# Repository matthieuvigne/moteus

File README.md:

# nautilus - a fork for moteus brushless servo driver

`nautilus` is a direct fork of moteus's driver with modified shape and interface to fit inside MyActuator's RMDX motors
(Mini-Cheatah like design), as a replacement of their driver. The main modifications are:

 - use an SPI interface instead of CAN
 - secondary SPI port for external encoder
 - usage of the `CSD88599` half-bridges instead of individual MOSFET to reduce the number of components
 - modified board shape and layout to fit inside the motor
 - the design is done using KiCad instead of Eagle

All new files are in the `nautilus` folder.

# moteus brushless servo #

This contains full designs for the moteus brushless servo actuator,
including firmware and PCBs.

**WARNING**: This is not just a software project.  It includes designs
for moderately high power electronics.  It has not yet burned down my
(or anyone's that I know of) house, but there are no guarantees.

# Specifications #

| Name                  | Value          |
|-----------------------|----------------|
| Voltage Input         | 10-44V         |
| Peak Electrical Power | 500W           |
| Mass                  | 14.2g          |
| Control Rate          | 15-40kHz       |
| PWM Switching Rate    | 15-60kHz       |
| CPU                   | 170Mhz STM32G4 |
| Peak phase current    | 100A           |
| Communications        | 5Mbps CAN-FD   |
| Dimensions            | 46x53mm        |

Assembled and tested boards can be purchased at https://mjbots.com/products/moteus-r4-11

# Directory structure #

* hw/ - hardware (mechanical and electrical designs)
  * controller/ - PCB design for servo controller
* fw/ - firmware for brushless controller
* lib/ - client side software
* utils/ - diagnostic tools
* tools/ - bazel build configure
* docs/ - documentation

# Documentation #

* [Getting Started](docs/getting_started.md)
* [Reference](docs/reference.md)

# Misc #

 * travis-ci 

# How to support moteus development #

The easiest way to support development the moteus hardware and firmware is as follows:

1) Buy things from https://mjbots.com
2) Build awesome machines!

That's it!  If for some reason you want to go above and beyond, you can sponsor mjbots through github: https://github.com/sponsors/mjbots

# License #

All files contained in this repository, unless otherwise noted, are
available under an Apache 2.0 License:
https://www.apache.org/licenses/LICENSE-2.0

# Trademark #

mjbots Robotic Systems LLC owns and protects the "mjbots" and "moteus" trademarks in many jurisdictions.

If you want to use these names in your project or product, please read the [Trademark Policy](https://mjbots.com/trademark-policy)

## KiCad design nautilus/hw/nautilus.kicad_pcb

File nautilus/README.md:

# How to compile and flash the firmware

## Installing dependencies

```sudo dnf install patch openocd arm-none-eabi-binutils-cs```

## Building the firmware

The firmware can be built by the following command:

```./tools/bazel test --config=target //fw:nautilus```

The bootloader also needs to be built (typically only once):

```./tools/bazel test --config=target //fw:can_bootloader ```

## Flashing

## Setting STM32 option bytes

Pin PB8 (boot) is used for I2C, thus pulled up. Hence, for the firmware to start running, the STM32 option bytes must be changed. This requires the software STM32CubeProgrammer, and the following configuration: nSWBOOT0 unchecked, nBOOT0 checked.

## Flashing

Simply run the python script: `python fw/flash.py`

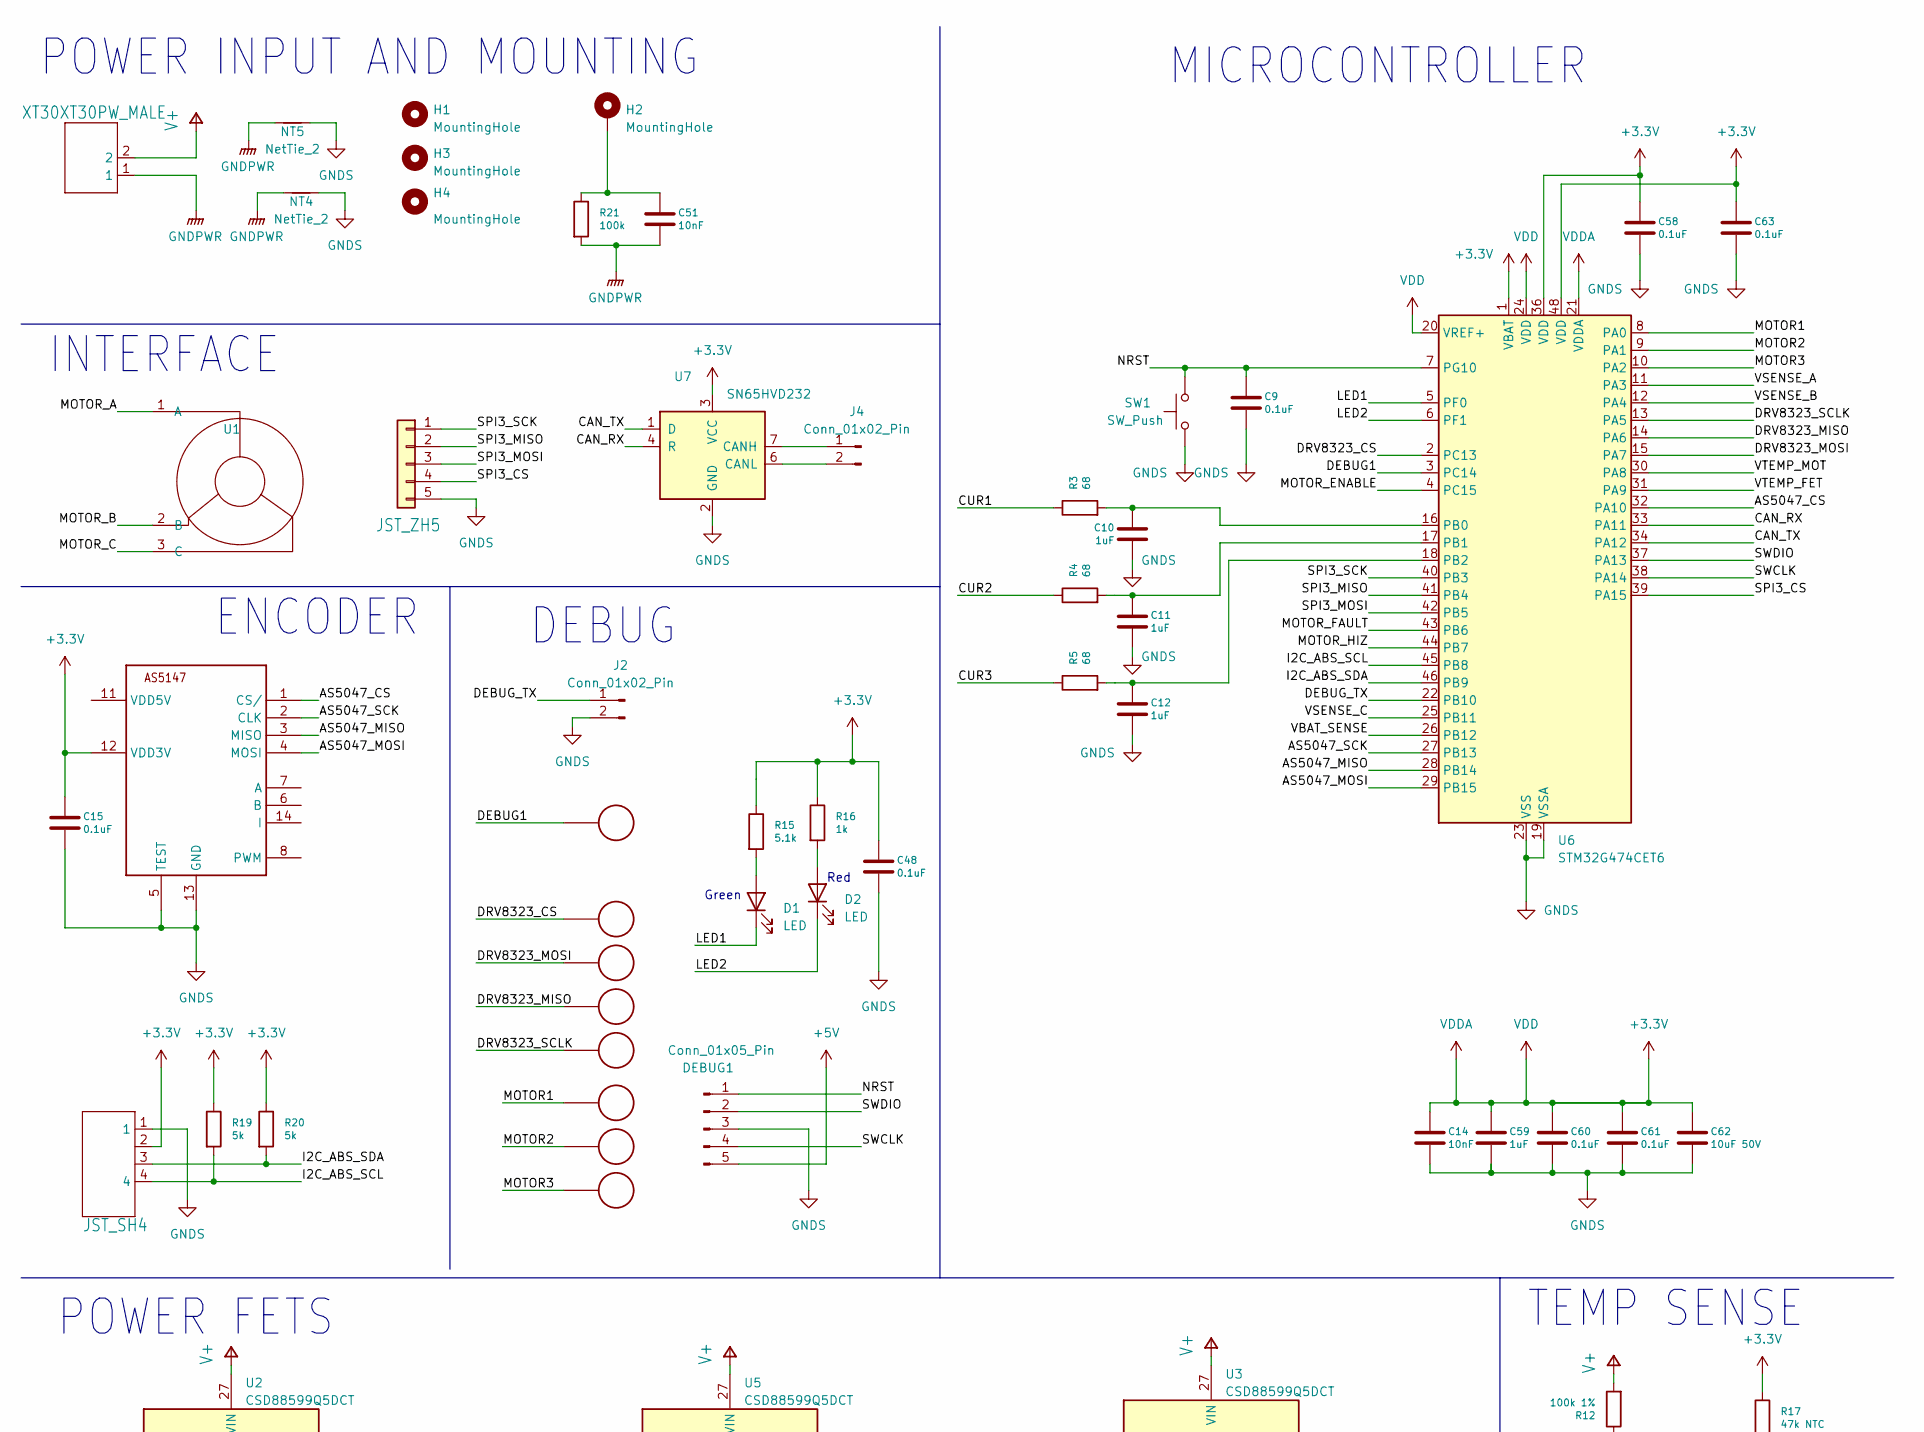
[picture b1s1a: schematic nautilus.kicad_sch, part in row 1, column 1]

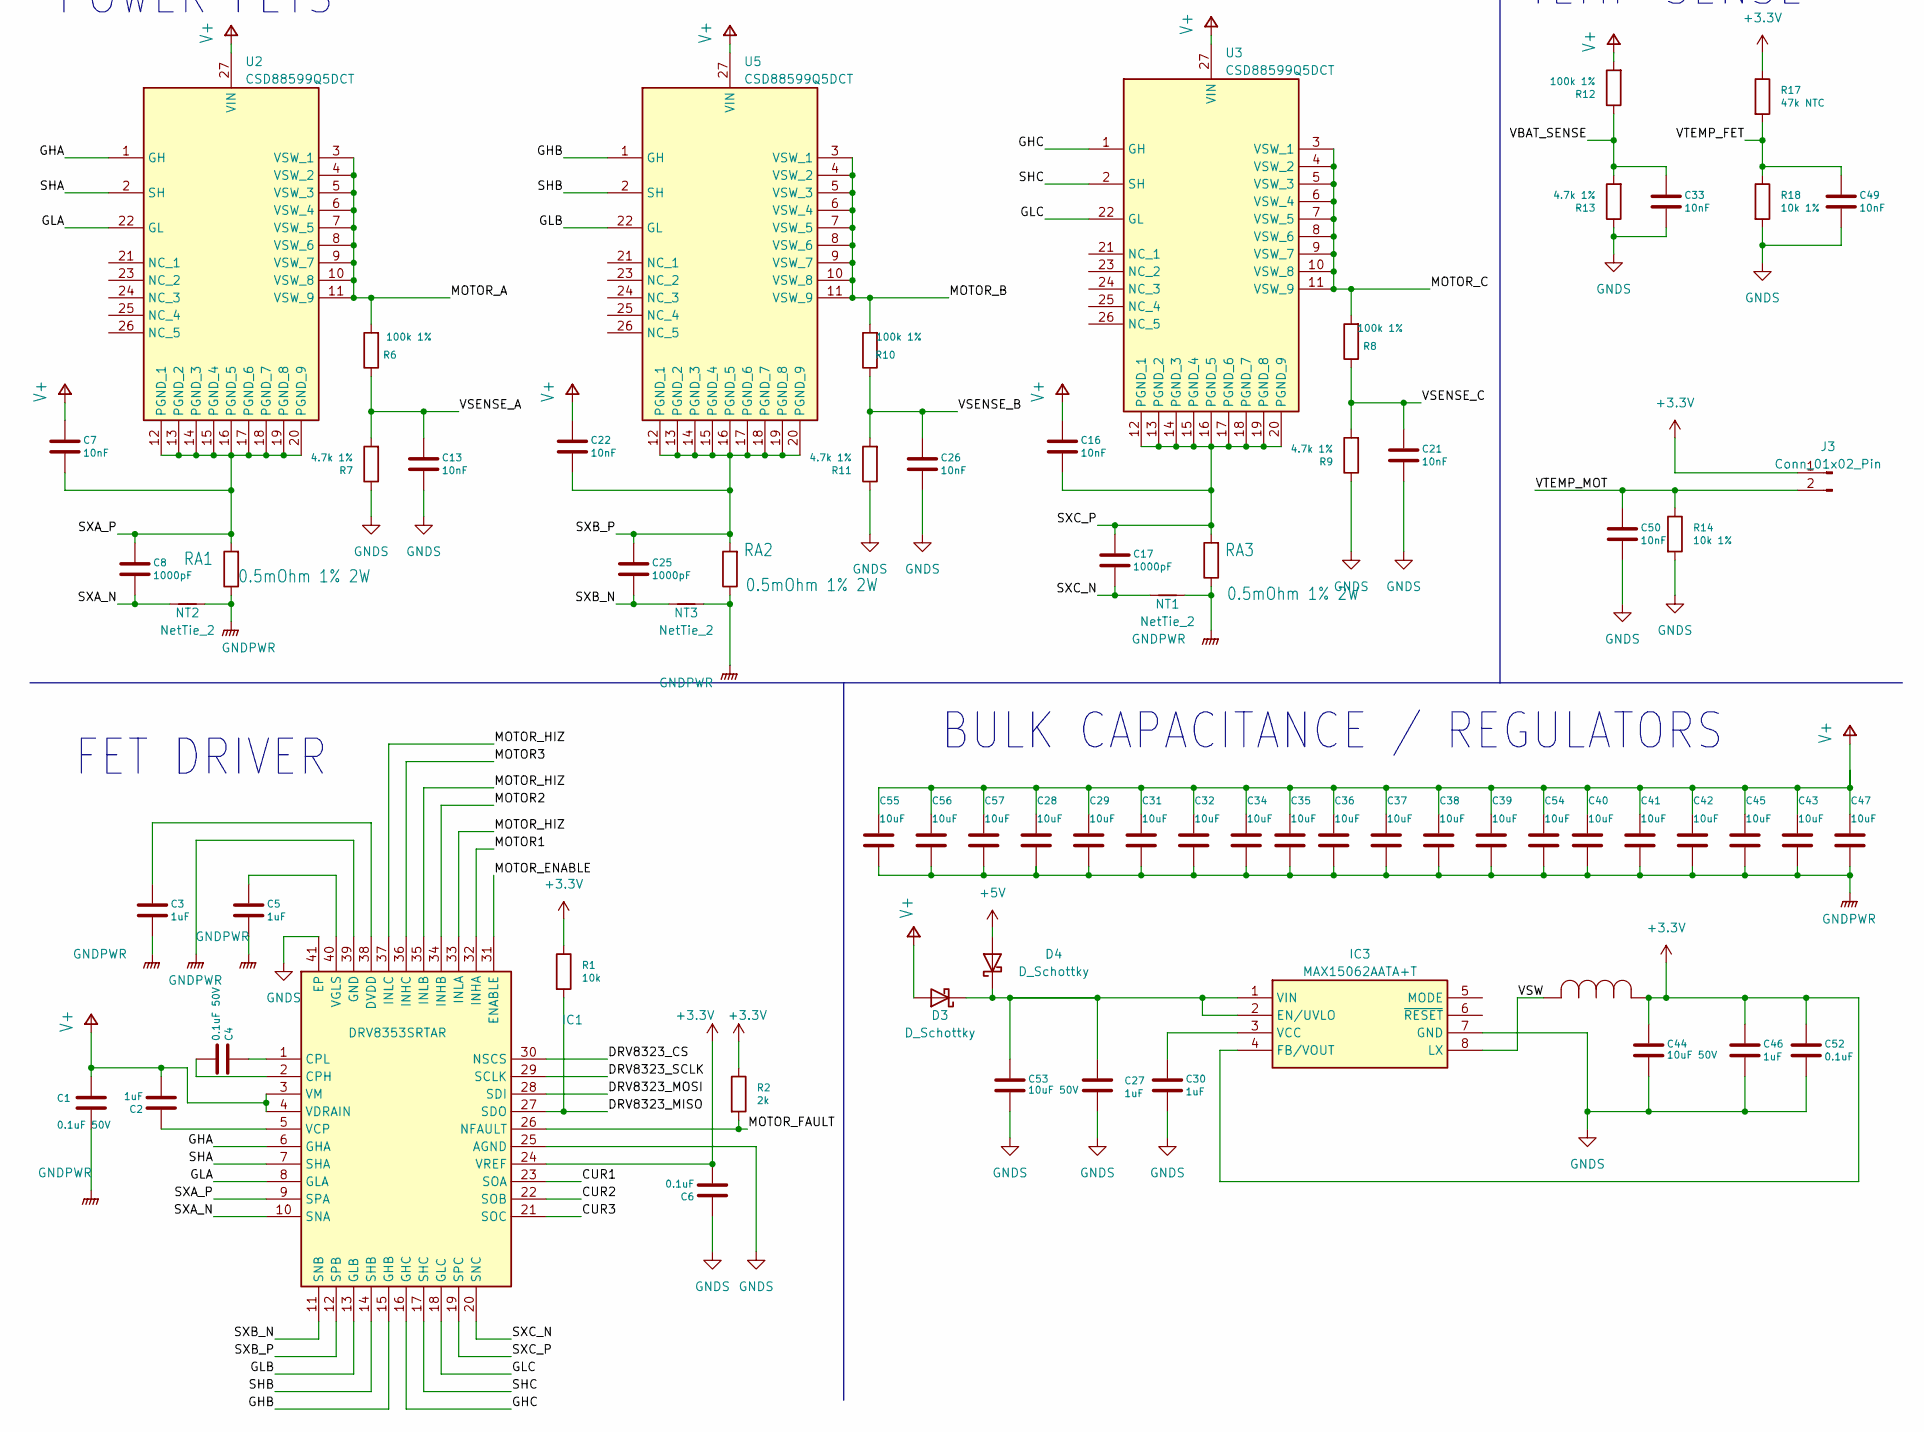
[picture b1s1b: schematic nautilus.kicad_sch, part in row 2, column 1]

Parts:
C1, C4: 0.1uF 50V; C_0402_1005Metric_Pad0.74x0.62mm_HandSolder; MPN CGA2B3X7R1H104K050BB
C2, C3, C5, C46, C59: 1uF; C_0402_1005Metric_Pad0.74x0.62mm_HandSolder; MPN MF-CAP-0402-1uF
C6, C9, C15, C48, C52, C58, C60, C61, C63: 0.1uF; C_0402_1005Metric_Pad0.74x0.62mm_HandSolder; MPN MF-CAP-0402-0.1uF
C7, C13, C14, C16, C21, C22, C26, C51: 10nF; C_0402_1005Metric_Pad0.74x0.62mm_HandSolder; MPN MF-CAP-0402-1nF
C8, C17, C25: 1000pF; C_0402_1005Metric_Pad0.74x0.62mm_HandSolder; MPN MF-CAP-0402-1nF
C10, C11, C12: 1uF; C_0402_1005Metric_Pad0.74x0.62mm_HandSolder; MPN MF-CAP-0402-1nF
C27, C30: 1uF; C_0402_1005Metric_Pad0.74x0.62mm_HandSolder; MPN MF-CAP-0603-1uF
C28, C29, C31, C32, C34, C35, C36, C37, C38, C39, C40, C41, C42, C43, C45, C47, C54, C55, C56, C57: 10uF; C_1206_3216Metric_Pad1.33x1.80mm_HandSolder; MPN CL31A106MBHNNNE; Mouser Part Number 187-CL31A106MBHNNNE
C33, C50: 10nF; C_0402_1005Metric_Pad0.74x0.62mm_HandSolder; MPN MF-CAP-0402-0.01uF
C44, C53, C62: 10uF 50V; C_1206_3216Metric_Pad1.33x1.80mm_HandSolder; MPN CL31A106MBHNNNE; Mouser Part Number 187-CL31A106MBHNNNE
C49: 10nF; C_0402_1005Metric_Pad0.74x0.62mm_HandSolder; MPN MF-CAP-0402-0.1uF
D1, D2: LED; LED_0805_2012Metric_Pad1.15x1.40mm_HandSolder
D3, D4: D_Schottky; D_SOD-123F; Mouser Part Number 833-SMD210PLQ-TP
DBG1: PAD24AWG_PAD; TestPoint_Pad_D1.0mm
DEBUG1: Conn_01x05_Pin; JST_SH_SM05B-SRSS-TB_1x05-1MP_P1.00mm_Horizontal
DRV_CS1: PAD24AWG_PAD; TestPoint_Pad_D1.0mm
DRV_MISO1: PAD24AWG_PAD; TestPoint_Pad_D1.0mm
DRV_MOSI1: PAD24AWG_PAD; TestPoint_Pad_D1.0mm
DRV_SCK1: PAD24AWG_PAD; TestPoint_Pad_D1.0mm
H1, H2, H3, H4: MountingHole; MountingHole-Plated
IC1: DRV8353SRTAR; QFN50P600X600X80-41N-D; Manufacturer_Part_Number DRV8353SRTAR; Mouser Part Number 595-DRV8353SRTAT
IC3: MAX15062AATA+T; MAX15062AATAT; Manufacturer_Part_Number MAX15062AATA+T; Mouser Part Number 700-MAX15062AATA+T
J1: XT30XT30PW_MALE; AMASS_XT30PW-M_1x02_P2.50mm_Horizontal
J2, J3: Conn_01x02_Pin; PinHeader_1x02_P2.54mm_Vertical
J4: Conn_01x02_Pin; Molex_PicoBlade_53047-0210_1x02_P1.25mm_Vertical
L1: SRN4018-220M; SRN4018220M; MANUFACTURER_PART_NUMBER SRN4018-330M; Mouser SRN4018
M1, M2, M3: PAD24AWG_PAD; TestPoint_Pad_D1.0mm
NT1, NT2, NT3, NT4, NT5: NetTie_2; NetTie-2_SMD_Pad0.5mm
R1: 10k; R_0402_1005Metric_Pad0.72x0.64mm_HandSolder; MPN MF-RES-0402-2K
R2: 2k; R_0402_1005Metric_Pad0.72x0.64mm_HandSolder; MPN MF-RES-0402-2K
R3, R4, R5: 68; R_0402_1005Metric_Pad0.72x0.64mm_HandSolder; MPN MF-RES-0402-22
R6, R8, R10, R12: 100k 1%; R_0402_1005Metric_Pad0.72x0.64mm_HandSolder; MPN RC0402FR-07100KL
R7, R9, R11, R13: 4.7k 1%; R_0402_1005Metric_Pad0.72x0.64mm_HandSolder; MPN RC0402FR-074K7L
R14, R18: 10k 1%; R_0402_1005Metric_Pad0.72x0.64mm_HandSolder; MPN RC0402FR-0710KL
R15: 5.1k; R_0402_1005Metric_Pad0.72x0.64mm_HandSolder; MPN MF-RES-0402-560
R16: 1k; R_0402_1005Metric_Pad0.72x0.64mm_HandSolder; MPN MF-RES-0402-560
R17: 47k NTC; R_0402_1005Metric_Pad0.72x0.64mm_HandSolder; MPN NCP15WB473F03RC; Mouser Part Number 81-NCP15WB473F03RC
R19, R20: 5k; R_0402_1005Metric_Pad0.72x0.64mm_HandSolder; MPN MF-RES-0402-2K
R21: 100k; R_0402_1005Metric_Pad0.72x0.64mm_HandSolder; MPN MF-RES-0402-2K
RA1, RA2, RA3: 0.5mOhm 1% 2W; R_2512_6332Metric_Pad1.40x3.35mm_HandSolder; MPN HCS1206FTL500; Mouser 504-MSMA2512R0005FGM
SPI1: JST_ZH5; JST_GH_SM05B-GHS-TB_1x05-1MP_P1.25mm_Horizontal; MPN S4B-ZR-SM4A-TF(LF)(SN)
SPI2: JST_SH4; JST_SH_SM04B-SRSS-TB_1x04-1MP_P1.00mm_Horizontal; MPN S4B-ZR-SM4A-TF(LF)(SN)
SW1: SW_Push; SW_SPST_B3U-1000P
U1: BrushlessMotor
U2, U3, U5: CSD88599Q5DCT; Q5DC_DMM; Manufacturer_Part_Number CSD88599Q5DCT; Mouser Part Number 595-CSD88599Q5DCT
U4: AS5147; TSSOP-14_4.4x5mm_P0.65mm; MPN AS5047P-ATSM
U6: STM32G474CET6; LQFP-48_7x7mm_P0.5mm; Mouser Part Number 511-STM32G474CET6
U7: SN65HVD232; SOIC-8_3.9x4.9mm_P1.27mm

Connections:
+3.3V: C6.2, C14.1, C15.1, C44.1, C46.1, C48.1, C52.1, C58.1, C59.1, C60.1, C61.1, C62.1, C63.1, IC1.24 (VREF), IC3.4 (FB/VOUT), J3.1, L1.1, R1.1, R2.1, R15.1, R16.1, R17.1, R19.1, R20.1, SPI2.2, U4.12 (VDD3V), U6.1 (VBAT), U6.20 (VREF+), U6.21 (VDDA), U6.24 (VDD), U6.36 (VDD), U6.48 (VDD), U7.3 (VCC)
+5V: D4.2 (A), DEBUG1.5
/AS5047_CS: U4.1 (CS/), U6.32 (PA10)
/AS5047_MISO: U4.3 (MISO), U6.28 (PB14)
/AS5047_MOSI: U4.4 (MOSI), U6.29 (PB15)
/AS5047_SCK: U4.2 (CLK), U6.27 (PB13)
/CAN_RX: U6.33 (PA11), U7.4 (R)
/CAN_TX: U6.34 (PA12), U7.1 (D)
/CUR1: IC1.23 (SOA), R3.1
/CUR2: IC1.22 (SOB), R4.1
/CUR3: IC1.21 (SOC), R5.1
/DEBUG1: DBG1.1, U6.3 (PC14)
/DEBUG_TX: J2.1, U6.22 (PB10)
/DRV8323_CS: DRV_CS1.1, IC1.30 (NSCS), U6.2 (PC13)
/DRV8323_MISO: DRV_MISO1.1, IC1.27 (SDO), R1.2, U6.14 (PA6)
/DRV8323_MOSI: DRV_MOSI1.1, IC1.28 (SDI), U6.15 (PA7)
/DRV8323_SCLK: DRV_SCK1.1, IC1.29 (SCLK), U6.13 (PA5)
/GHA: IC1.6 (GHA), U2.1 (GH)
/GHB: IC1.15 (GHB), U5.1 (GH)
/GHC: IC1.16 (GHC), U3.1 (GH)
/GLA: IC1.8 (GLA), U2.22 (GL)
/GLB: IC1.13 (GLB), U5.22 (GL)
/GLC: IC1.18 (GLC), U3.22 (GL)
/I2C_ABS_SCL: R19.2, SPI2.4, U6.45 (PB8)
/I2C_ABS_SDA: R20.2, SPI2.3, U6.46 (PB9)
/LED1: D1.1 (K), U6.5 (PF0)
/LED2: D2.1 (K), U6.6 (PF1)
/MOTOR1: IC1.32 (INHA), M1.1, U6.8 (PA0)
/MOTOR2: IC1.34 (INHB), M2.1, U6.9 (PA1)
/MOTOR3: IC1.36 (INHC), M3.1, U6.10 (PA2)
/MOTOR_A: R6.2, U1.1 (A), U2.3 (VSW_1), U2.4 (VSW_2), U2.5 (VSW_3), U2.6 (VSW_4), U2.7 (VSW_5), U2.8 (VSW_6), U2.9 (VSW_7), U2.10 (VSW_8), U2.11 (VSW_9)
/MOTOR_B: R10.2, U1.2 (B), U5.3 (VSW_1), U5.4 (VSW_2), U5.5 (VSW_3), U5.6 (VSW_4), U5.7 (VSW_5), U5.8 (VSW_6), U5.9 (VSW_7), U5.10 (VSW_8), U5.11 (VSW_9)
/MOTOR_C: R8.2, U1.3 (C), U3.3 (VSW_1), U3.4 (VSW_2), U3.5 (VSW_3), U3.6 (VSW_4), U3.7 (VSW_5), U3.8 (VSW_6), U3.9 (VSW_7), U3.10 (VSW_8), U3.11 (VSW_9)
/MOTOR_ENABLE: IC1.31 (ENABLE), U6.4 (PC15)
/MOTOR_FAULT: IC1.26 (NFAULT), R2.2, U6.43 (PB6)
/MOTOR_HIZ: IC1.33 (INLA), IC1.35 (INLB), IC1.37 (INLC), U6.44 (PB7)
/NRST: C9.1, DEBUG1.1, SW1.2, U6.7 (PG10)
/SHA: IC1.7 (SHA), U2.2 (SH)
/SHB: IC1.14 (SHB), U5.2 (SH)
/SHC: IC1.17 (SHC), U3.2 (SH)
/SPI3_CS: SPI1.4, U6.39 (PA15)
/SPI3_MISO: SPI1.2, U6.41 (PB4)
/SPI3_MOSI: SPI1.3, U6.42 (PB5)
/SPI3_SCK: SPI1.1, U6.40 (PB3)
/SWCLK: DEBUG1.4, U6.38 (PA14)
/SWDIO: DEBUG1.2, U6.37 (PA13)
/SXA_N: C8.2, IC1.10 (SNA), NT2.2
/SXA_P: C7.2, C8.1, IC1.9 (SPA), RA1.2, U2.12 (PGND_1), U2.13 (PGND_2), U2.14 (PGND_3), U2.15 (PGND_4), U2.16 (PGND_5), U2.17 (PGND_6), U2.18 (PGND_7), U2.19 (PGND_8), U2.20 (PGND_9)
/SXB_N: C25.2, IC1.11 (SNB), NT3.2
/SXB_P: C22.2, C25.1, IC1.12 (SPB), RA2.2, U5.12 (PGND_1), U5.13 (PGND_2), U5.14 (PGND_3), U5.15 (PGND_4), U5.16 (PGND_5), U5.17 (PGND_6), U5.18 (PGND_7), U5.19 (PGND_8), U5.20 (PGND_9)
/SXC_N: C17.2, IC1.20 (SNC), NT1.2
/SXC_P: C16.2, C17.1, IC1.19 (SPC), RA3.2, U3.12 (PGND_1), U3.13 (PGND_2), U3.14 (PGND_3), U3.15 (PGND_4), U3.16 (PGND_5), U3.17 (PGND_6), U3.18 (PGND_7), U3.19 (PGND_8), U3.20 (PGND_9)
/VBAT_SENSE: C33.1, R12.1, R13.2, U6.26 (PB12)
/VSENSE_A: C13.1, R6.1, R7.2, U6.11 (PA3)
/VSENSE_B: C26.1, R10.1, R11.2, U6.12 (PA4)
/VSENSE_C: C21.1, R8.1, R9.2, U6.25 (PB11)
/VSW: IC3.8 (LX), L1.2
/VTEMP_FET: C49.1, R17.2, R18.1, U6.31 (PA9)
/VTEMP_MOT: C50.1, J3.2, R14.1, U6.30 (PA8)
GNDPWR: C1.2, C3.2, C5.2, C28.2, C29.2, C31.2, C32.2, C34.2, C35.2, C36.2, C37.2, C38.2, C39.2, C40.2, C41.2, C42.2, C43.2, C45.2, C47.2, C51.2, C54.2, C55.2, C56.2, C57.2, IC1.39 (GND), J1.1, NT1.1, NT2.1, NT3.1, NT4.2, NT5.2, R21.2, RA1.1, RA2.1, RA3.1
GNDS: C6.1, C9.2, C10.2, C11.2, C12.2, C13.2, C14.2, C15.2, C21.2, C26.2, C27.2, C30.2, C33.2, C44.2, C46.2, C48.2, C49.2, C50.2, C52.2, C53.2, C58.2, C59.2, C60.2, C61.2, C62.2, C63.2, DEBUG1.3, IC1.25 (AGND), IC1.41 (EP), IC3.7 (GND), J2.2, NT4.1, NT5.1, R7.1, R9.1, R11.1, R13.1, R14.2, R18.2, SPI1.5, SPI2.1, SW1.1, U4.5 (TEST), U4.13 (GND), U6.19 (VSSA), U6.23 (VSS), U6.35 (VSS), U6.47 (VSS), U7.2 (GND)
unnamed: C51.1, H2.1, R21.1
unnamed: D1.2 (A), R15.2
unnamed: D2.2 (A), R16.2
unnamed: C27.1, C53.1, D3.1 (K), D4.1 (K), IC3.1 (VIN), IC3.2 (EN/UVLO)
unnamed: C4.2, IC1.2 (CPH)
unnamed: C4.1, IC1.1 (CPL)
unnamed: C3.1, IC1.38 (DVDD)
unnamed: C2.1, IC1.5 (VCP)
unnamed: C5.1, IC1.40 (VGLS)
unnamed: C30.1, IC3.3 (VCC)
unnamed: J4.1, U7.7 (CANH)
unnamed: J4.2, U7.6 (CANL)
unnamed: C10.1, R3.2, U6.16 (PB0)
unnamed: C11.1, R4.2, U6.17 (PB1)
unnamed: C12.1, R5.2, U6.18 (PB2)
V+: C1.1, C2.2, C7.1, C16.1, C22.1, C28.1, C29.1, C31.1, C32.1, C34.1, C35.1, C36.1, C37.1, C38.1, C39.1, C40.1, C41.1, C42.1, C43.1, C45.1, C47.1, C54.1, C55.1, C56.1, C57.1, D3.2 (A), IC1.3 (VM), IC1.4 (VDRAIN), J1.2, R12.2, U2.27 (VIN), U3.27 (VIN), U5.27 (VIN)

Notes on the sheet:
Green
INTERFACE
POWER INPUT AND MOUNTING
TEMP SENSE
ENCODER
Red
MICROCONTROLLER
FET DRIVER
BULK CAPACITANCE / REGULATORS
DEBUG
POWER FETS

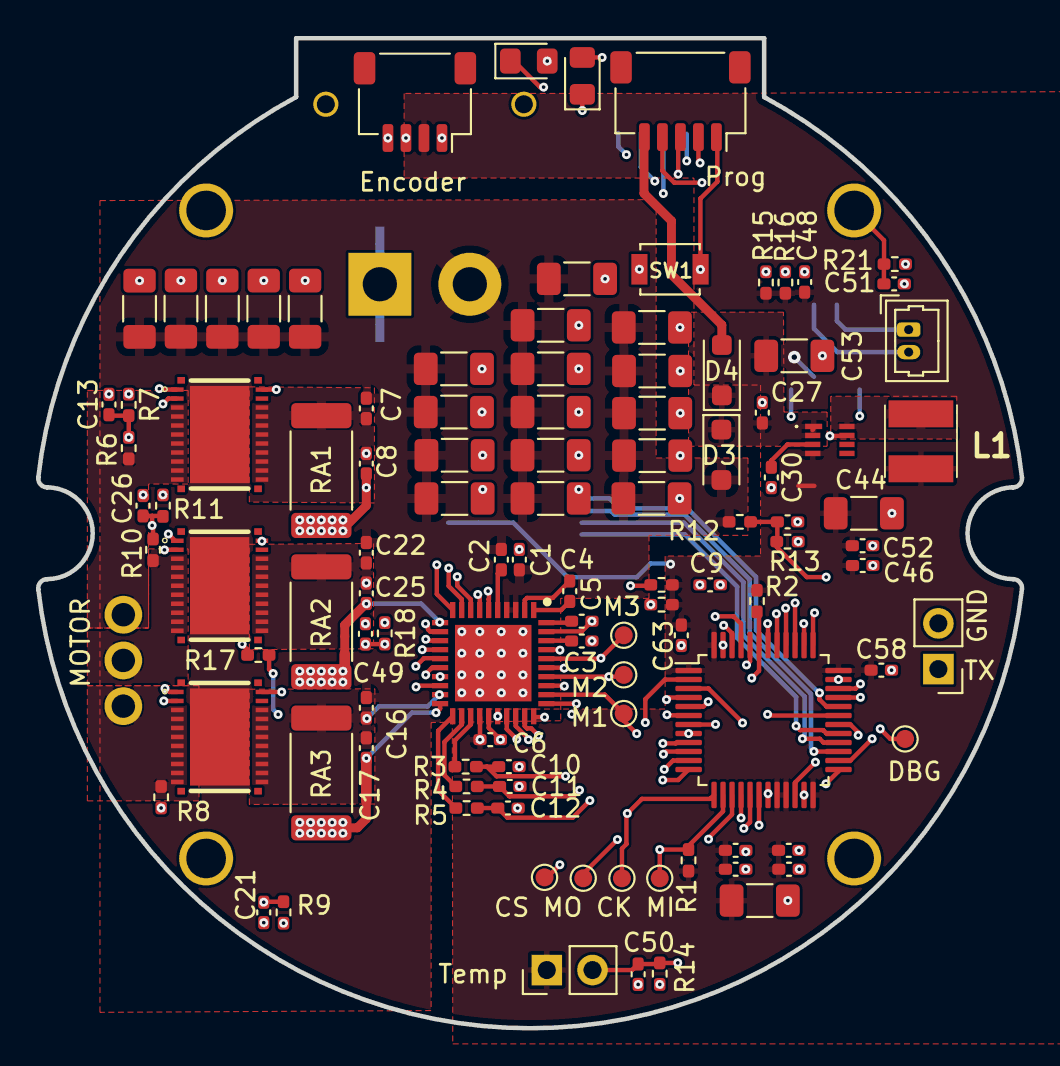
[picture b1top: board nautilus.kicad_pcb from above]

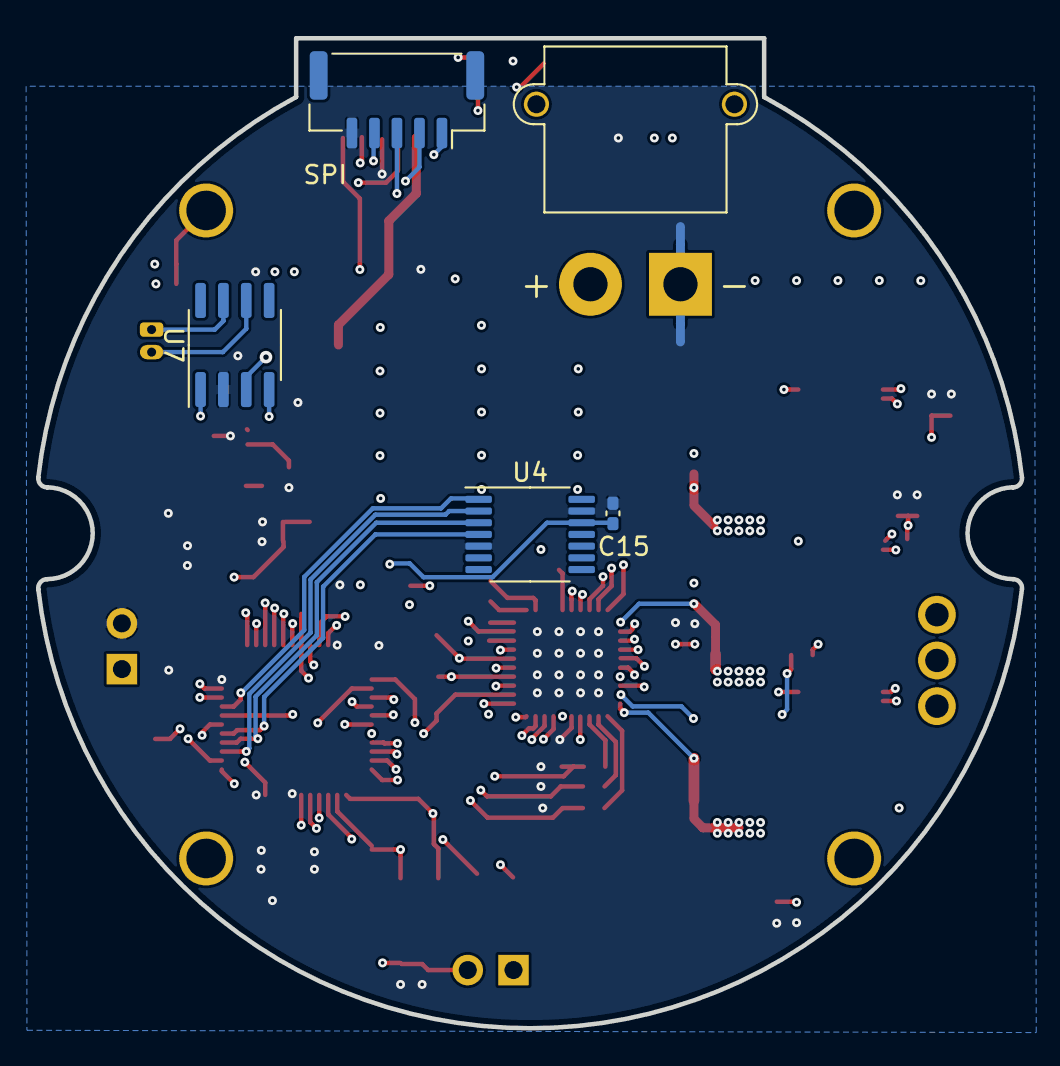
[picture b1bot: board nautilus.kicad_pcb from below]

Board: 4 copper layers, 54.7 x 55.0 mm, 121 parts (7 on the bottom side), 77 nets.

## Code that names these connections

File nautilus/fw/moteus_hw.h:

// Copyright 2018-2022 Josh Pieper, jjp@pobox.com.
//
// Licensed under the Apache License, Version 2.0 (the "License");
// you may not use this file except in compliance with the License.
// You may obtain a copy of the License at
//
//     http://www.apache.org/licenses/LICENSE-2.0
//
// Unless required by applicable law or agreed to in writing, software
// distributed under the License is distributed on an "AS IS" BASIS,
// WITHOUT WARRANTIES OR CONDITIONS OF ANY KIND, either express or implied.
// See the License for the specific language governing permissions and
// limitations under the License.

#pragma once

#include "mbed.h"

#include "fw/millisecond_timer.h"

namespace moteus {

//////////////////////////////////////////
// The following "families" are supported:
//  moteus    - family 0
//  moteus_hp - family 1
//
// Each family has an independent hardware version timeline, and
// possibly a different mechanism for verifying hardware version
// compatibility.


// This structure is filled in once the family and hardware version
// are known.
struct MoteusHwPins {
  PinName pwm1 = PA_0_ALT0;
  PinName pwm2 = PA_1_ALT0;
  PinName pwm3 = PA_2_ALT0;

  PinName drv8323_enable = NC;
  PinName drv8323_hiz = NC;
  PinName drv8323_cs = NC;

  PinName drv8323_mosi = NC;
  PinName drv8323_miso = NC;
  PinName drv8323_sck = NC;
  PinName drv8323_fault = NC;

  PinName debug_led1 = NC;
  PinName status_led = NC;

  PinName current1 = NC;
  PinName current2 = NC;
  PinName current3 = NC;

  PinName vsense = NC;
  PinName tsense = PA_9;

  PinName msense = NC;

  float vsense_adc_scale = 0.0f;

  PinName uart_tx = NC;
  PinName uart_rx = NC;
  PinName uart_dir = NC;

  PinName as5047_cs = NC;

  PinName can_td = NC;
  PinName can_rd = NC;

  PinName debug1 = NC;
  PinName debug2 = NC;
  PinName debug_dac = NC;

  uint32_t model_number = 0;

  uint32_t firmware_version = 0x000105;
};


struct FamilyAndVersion {
  int family = 0;
  int hw_version = 0;
  int hw_pins = 0;
};

// Return what family we are executing on.
FamilyAndVersion DetectMoteusFamily(MillisecondTimer*);

MoteusHwPins FindHardwarePins(FamilyAndVersion);


// The "FIRMWARE_VERSION" is a misnomer.  It instead is the equivalent
// of an ABI version, and is incremented when configuration values
// change in a way that would not result in equivalent behavior across
// an upgrade/downgrade.

// Version history:

// # 0x0101 #
//
// * Fixed the calculation of feedforward voltage to have the correct
//   sign for the velocity component.  Previous firmwares,
//   inappropriately applied a negative feedforward term, which
//   counteracted rotation instead of being an actual feedforward.

// # 0x0102 #
//
// * Removed servo.feedforward_scale entirely

// # 0x0103 #
//
// * Added servo.pwm_scale, and for r4.8 boards changed the default
//   value of pwm_comp_off / pwm_comp_mag.

// # 0x0104 #
//
// * Added configurable PWM rates, which changed default values of
//   pwm_comp_mag and pwm_comp_off.

// # 0x0105 #
//
// * Switched to a new encoder and position subsystem.

#define MOTEUS_MODEL_NUMBER 0x0000
#define MOTEUS_FIRMWARE_VERSION 0x000105

extern MoteusHwPins g_hw_pins;

}

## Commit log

2023-06-18 Start of Nautilus project
    Migrate schematic from Eagle to Kicad.
    Schematic modifications: introduce CSD88599Q5DC, remove CAN port.
    Tentative PCB layout.
2023-07-09 First PCB layout, before DRC.
2023-07-09 First PCB design passing DRC
2023-07-14 Cleanup PCB before order
2023-07-16 Minor PCB update
2023-07-16 [Hardware] First prototype order
2023-08-01 Add base FW (moteus)
2023-08-01 Update pin mapping to be compatible with nautilus
2023-08-03 POC of spi communication
2023-08-03 POC of frame transfer. RX works, TX live updates work, but the TX buffer is not flushed...
2023-08-04 Clear SPI Tx buffer on SS high
2023-08-27 First prototype assembly
    - [hw] Fix reverse XT-30 connector in PCB
    - [sw] Add led blink to SPI communication
    - [sw] Add note about using SPI1 mode only (other modes don't work)
2023-09-02 Add dummy SPI read function
2023-09-05 Start filling SPI read function
2023-09-07 SPI: add temperature reading
2023-09-09 Aux port configuration: hard-code AS5048 as secondary sensor and send reading to SPI
2023-09-09 Add I2C disconnect detection
2023-09-09 Hard-code default motor config
2023-09-12 Begin support for write command. Assign true debug role to the onboard LEDs. Fix some incorrect read instructions.
2023-09-19 Add RaspberryPi driver & GUI. Begining of work on getting the commutation working on the motor.
2023-09-22 Add DRV debug register to SPI register list.
2023-09-22 [NautilusGUI] Rework register list.
2023-09-24 [NautilusGUI] Add commutation strategy (WIP, not saved to drive)
2023-09-27 [NautilusGUI] Add code for servo control, with plotting using Teleplot.
2023-09-29 Working POC, in position and current mode.
    - Improve commutation algorithm by performing gradual motion.
    - Remove position limit and current derate from driver.
    - Add possibility to update control gains from SPI.
    Note: commutation parameters are currently not stored to persistent memory.
2023-09-30 Add button to save the configuration to the flash memory.
2023-09-30 NautilusGUI: code cleanup, fix termination segfault.
2023-10-02 NautilusGUI: add TextView to show log messages.
2023-10-03 [fw] Add velocity control mode. Configure default parameters for the RMDXV2 motor.
    Bugfixes and improvement to the GUI.
2023-10-05 [NautilusGUI] Various improvements
    - Keep spi port open
    - Monitor motor state, and stop generating signal on error
2023-10-07 Optimize SPI timing: clock speed up to 8MHz have been successfully tested.
2023-10-08 [Hardware] PCB V2: new layout, using LQFP package for microcontroller.
2023-10-09 [fw] Return motor integrated position instead of encoder single-turn value.
    Position and velocity target now in rad.
    Update control gains.
2023-10-29 [Hardware] V2 board order
2023-12-21 Minor PCB fixup
2023-12-25 Add missing build files. Update resistor value for led brightness.
2023-12-25 Various firmware fixup
    - Checksum: use 1 complement
    - Add firmware version register
    - Improve 'store to persistent config' option: though it only works once then crashes,
    at least the new version compiles using 'vanilla' external lib version
2023-12-25 Reduce position pll filter frequency to 100Hz. Add picture of PCB prototype.
2024-01-06 [NautilusGui] Add sendInvalidCommand to test feature & red led
2024-08-26 Update current sense filtering to 14kHz to avoid aliasing.
2024-10-04 Update control gains to match new current filter. Make number of poles writable.
2024-10-04 Add capability to configure gate drive current remotely.
2024-10-17 Add debug option to freeze encoder position.
